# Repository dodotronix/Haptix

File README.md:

## HAPTIX

### INSTALL
* install Archlinux on SD card (https://archlinuxarm.org/platforms/armv6/raspberry-pi)
* turn on RPi
* use ssh or keyboard and display to continue in installation

* update system with
> pacman -Syu
* download 
> pacman -S python 
* download snap shot from link: https://aur.archlinux.org/packages/python-spidev/
* open terminal -> cd /path/to/file -> tar xzf file-name -> cd file-name ->
makepkg -s -> sudo pacman -U name-of-file.pkg.tar.xz
* copy test.py to raspberry
* cd /path/to/test.py
* chmod +x test.py
* ./test.py
* you select functions in script, which you want to run

### NOTES
* spidev doc (https://github.com/doceme/py-spidev)
* raspberry ssh command: ssh alarm@10.0.4.x, password: "alarm" (custom settings)
* sudo iptables -t nat -vnL
* setup.sh creates nat, starts dhcpcd, launchs ssh (parameters: on/off)

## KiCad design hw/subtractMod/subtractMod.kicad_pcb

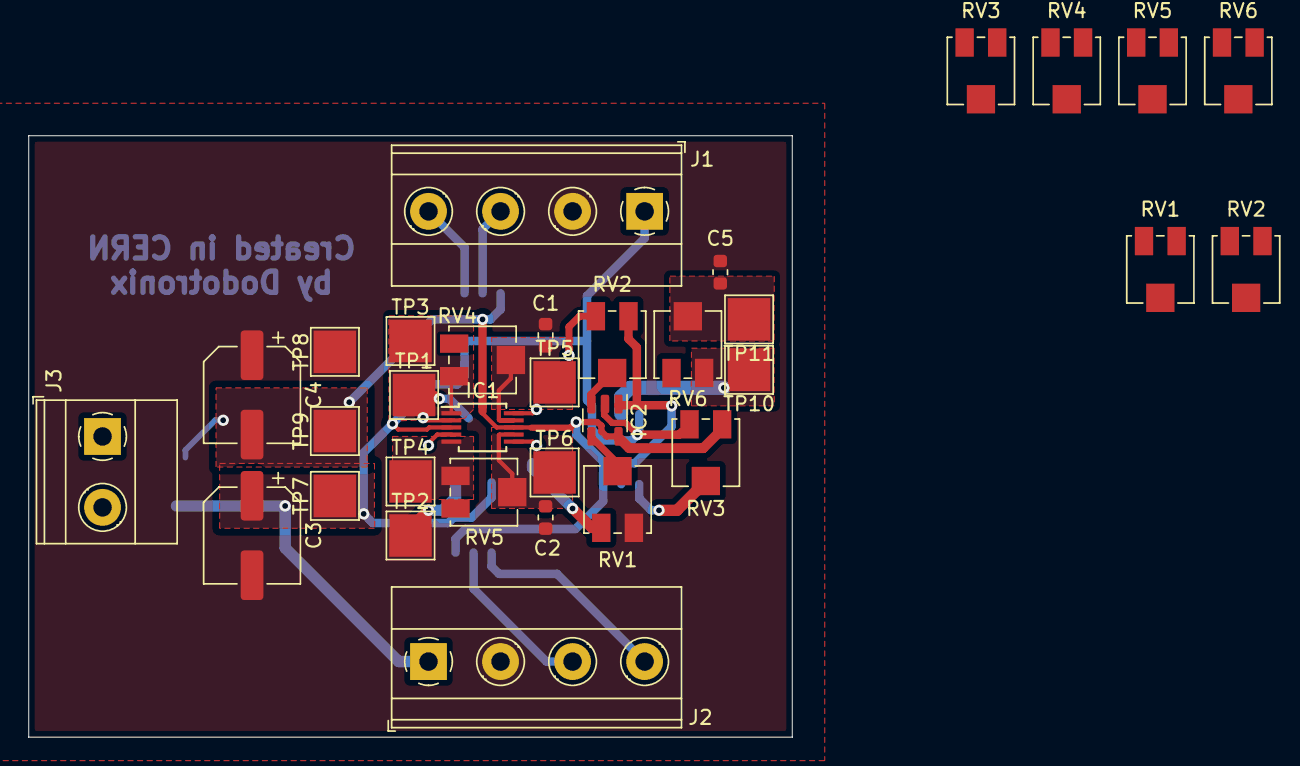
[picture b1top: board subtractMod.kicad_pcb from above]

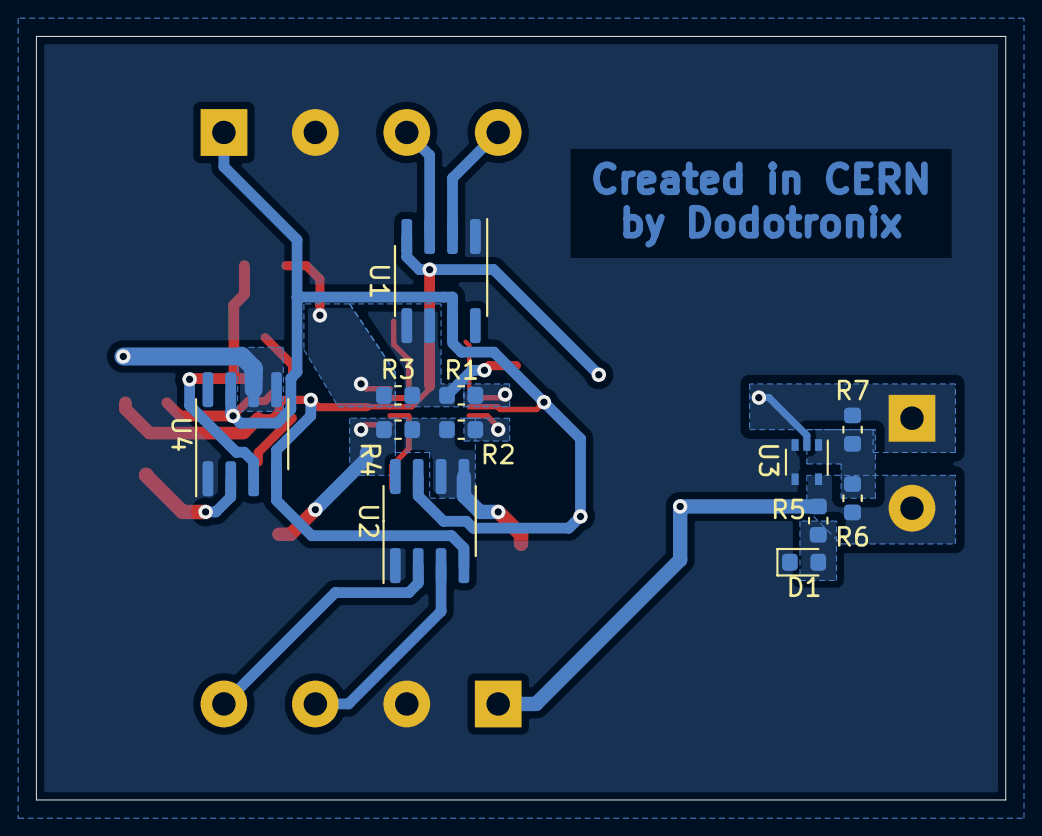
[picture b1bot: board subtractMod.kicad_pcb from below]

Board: 2 copper layers, 53.8 x 42.4 mm, 45 parts (12 on the bottom side), 25 nets.

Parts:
C1, C2, C5: C; C_0603_1608Metric
C3, C4: 47u; CP_Elec_6.3x5.9
D1: LED; LED_0603_1608Metric
IC1: AD8244; MSOP-10_3x3mm_P0.5mm
IC2: LMP2011; SOT-23-5
J1, J2: Screw_Terminal_01x04; TerminalBlock_Phoenix_MKDS-1,5-4-5.08_1x04_P5.08mm_Horizont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
J3: Screw_Terminal_01x02; TerminalBlock_Phoenix_MKDS-1,5-2_1x02_P5.00mm_Horizontal
R1, R2, R3, R4: 0R; R_0603_1608Metric
R5: R; R_0603_1608Metric
R6, R7: 10k; R_0603_1608Metric
RV1, RV2, RV3, RV4, RV5, RV6: R_POT_TRIM; Potentiometer_Bourns_3314J_Vertical
RV1#2, RV2#2, RV3#2, RV4#2, RV5#2, RV6#2: R_Potentiometer_Trim; Potentiometer_Bourns_3314J_Vertical
TP1, TP2, TP3, TP4, TP5, TP6, TP7, TP8, TP9, TP10, TP11: TestPoint; TestPoint_Pad_3.0x3.0mm
U1, U2, U4: AD8276; SOIC-8_3.9x4.9mm_P1.27mm
U3: TLV6001DCK; SOT-353_SC-70-5

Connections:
+5V: C3.1, IC1.3 (+V), IC2.5 (+V), J1.1, J2.1, J3.2, R5.1, R6.1, RV3.3, RV5#2.1, TP7.1, U1.7 (V+), U2.7 (V+), U3.5 (V+), U4.7 (V+)
-5V: C4.2, IC1.8 (-V), IC2.2 (-V), J3.1, R7.2, RV3.1, RV5#2.3, TP9.1, U1.4 (V-), U2.4 (V-), U3.2 (V-), U4.4 (V-)
/Input_channel/chan1_out: IC1.4 (OutB), R3.1, RV3#2.3
/Input_channel/chan2_out: IC1.9 (OutD), R4.1, RV4#2.1
/Input_channel/sensA_out: R1.2, R3.2, TP1.1, U1.5 (SENSE), U1.6
/Input_channel/sensB_out: R2.2, R4.2, TP2.1, U2.5 (SENSE), U2.6
GND: C1.2, C2.2, C3.2, C4.1, C5.2, D1.1 (K), J1.2, J2.2, RV1.3, RV4#2.3, TP8.1, U1.1 (REF), U2.1 (REF), U3.3 (-), U3.4, U4.1 (REF)
unnamed: C5.1, RV6.2, RV6#2.2, TP11.1
unnamed: D1.2 (A), R5.2
unnamed: IC1.1 (InA), R1.1
unnamed: IC1.2 (OutA), RV1#2.1, TP3.1
unnamed: C1.1, IC1.5 (InB), RV1#2.2, TP5.1
unnamed: IC1.6 (InC), R2.1
unnamed: IC1.7 (OutC), RV2#2.1, TP4.1
unnamed: C2.1, IC1.10 (InD), RV2#2.2, TP6.1
unnamed: IC2.3 (V+), RV3#2.2
unnamed: IC2.4 (V-), RV4#2.2
unnamed: IC2.1 (Vout), RV3#2.1, U4.3 (+)
unnamed: J1.3, U1.3 (+)
unnamed: J1.4, U1.2 (-)
unnamed: J2.3, U2.3 (+)
unnamed: J2.4, U2.2 (-)
unnamed: R6.2, R7.1, U3.1 (+)
unnamed: RV5#2.2, U4.2 (-)
unnamed: RV6#2.1, TP10.1, U4.5 (SENSE), U4.6

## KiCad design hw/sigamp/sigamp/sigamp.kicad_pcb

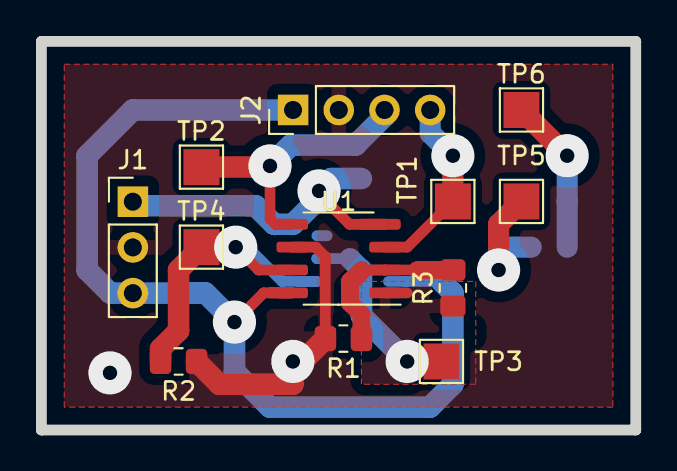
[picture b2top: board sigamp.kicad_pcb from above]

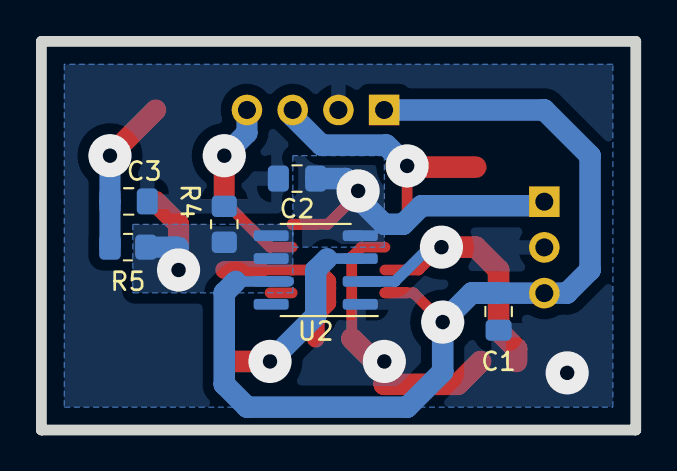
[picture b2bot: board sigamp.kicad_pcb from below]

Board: 2 copper layers, 33.0 x 21.6 mm, 18 parts (6 on the bottom side), 10 nets.

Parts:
C1, C2: 100n; C_0805_2012Metric_Pad1.18x1.45mm_HandSolder
C3: C; C_0805_2012Metric_Pad1.18x1.45mm_HandSolder
J1: Conn_01x03; PinHeader_1x03_P2.54mm_Vertical
J2: Conn_01x04; PinHeader_1x04_P2.54mm_Vertical
R1, R2, R3, R4, R5: R; R_0805_2012Metric_Pad1.20x1.40mm_HandSolder
TP1, TP2, TP3, TP4, TP5, TP6: TestPoint; TestPoint_Pad_2.0x2.0mm
U1: LM358; SO-8_3.9x4.9mm_P1.27mm
U2: AD8276; SOIC-8_3.9x4.9mm_P1.27mm

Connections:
+5V: C1.1, J1.3, J2.1, U1.8 (V+), U2.7 (V+)
-5V: C2.1, J1.1, U1.4 (V-), U2.4 (V-)
/s+: J2.4, TP1.1, U1.3 (+)
/s-: J2.3, TP2.1, U1.5 (+)
GND: C1.2, C2.2, C3.2, J1.2, J2.2, R1.2, R2.1, R4.1, U1.6 (-), U2.1 (REF)
unnamed: C3.1, R5.1, TP6.1
unnamed: R1.1, R3.2, U1.2 (-)
unnamed: R2.2, TP4.1, U1.7, U2.2 (-)
unnamed: R3.1, TP3.1, U1.1, U2.3 (+)
unnamed: R4.2, R5.2, TP5.1, U2.5 (SENSE), U2.6

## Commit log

2018-12-14 new project
2018-12-14 new readme
2018-12-18 spi test
2018-12-19 hardware photos
2018-12-24 new functions
2018-12-26 installation guide
2018-12-26 new functions in script for analysis
2018-12-26 scheme of wiring of DUT
2020-02-29 pcb for signal subtraction test
2020-02-29 new gitignore
2020-03-02 changed tracks width
2020-03-11 added component webpages and datasheets
2020-03-11 reorganizing of onboard pins
2021-06-15 signal amplifier for load cell sensor reliability test
2024-09-06 created new empty script to simulate kinematics of the grinder
2024-09-10 basic speed chart respecting the system parameters
2024-09-10 fixed wrong calculation of the decelation stage
2024-09-10 finished simulation of the speed when the movable part reaches the top
2024-09-11 model is now reacting to change of the tool height
2024-09-13 refactored kinematic_model script and renamed to demo.m
2024-09-13 adjusted plots to be easier to read
2024-09-13 added gforce
2024-09-13 added force chart which we need for further simulation
2024-09-13 added contra force signal, that is simulating the force applied to the tool from above
2024-09-14 fixed problem with cumtrapez, which did not return correct number of values
2024-09-14 removed redundant printouts
2024-09-14 messing around with possible scenarios of interference
2024-09-17 blink test python script using ft232h
2024-09-17 added i2c class to control the accelerometer
2024-09-17 added makefile to install important libraries and packages
2024-09-17 prototype of pkgbuild for bno08x library for archlinux
2024-09-17 package to build latest circuitpython bno08x library
2024-09-17 busdevice pkgbuild moved to dedicated folder
2024-09-17 created new arch package circuitpython-busdevice
2024-09-17 created new package circuitpython-typing
2024-09-18 fixed wrong name of the adafruit python package
2024-09-21 tested different speeds of i2c - chip uses stretching and lower clock speed does not work
2024-09-21 added spi, it seems to be responding, but the ft232h bridge does not support cpha=1
2024-09-21 ft232h seems to work with mpu6050 accelerometer
2024-09-21 new bno08x circuitpython library for archlinux
2024-09-21 new mpu6050 circuitpython library for archlinux
2024-09-21 new circuitpython register library for archlinux
2024-09-25 deleted redundant bno08x package
2024-09-25 fixed wrong conflits and added suffix git to each directory
2024-09-25 missing circuitpython in the package name
2024-09-28 added pyvisa to dependencies
2024-09-28 script reading waveform from my rigol oscilloscope
2024-09-30 updated kicad file version
2024-10-05 scripts for haptix tests
2024-10-05 updated schematics of subtraction module
2024-10-14 removed ft232h bridge
2024-10-14 created circuit python accelerometer and storage test
2024-10-17 added network configuration to connect rigol to my computer
2024-10-18 working measurement setup
2024-10-18 measurement in micrometers of the force sensor
2024-10-22 load cell and accelerometer tests
2024-10-25 last code.py update
2024-11-19 removed redundant measurements
2024-11-20 removed nonsens data
2024-11-20 created demo for analyzing measured data
2024-11-21 substraction demo script to test detection method
2024-11-22 unsorted force measurements moved to touch_4 folder
2024-11-22 light hand touches analysis
2024-11-24 data measured with the ltc2440 moved to the other measurements
2024-11-24 reorganized data loading
2024-11-24 created test to analyze interferences - not working, because of incorrect data collection for the first test
2024-11-30 kalman filter test from the book
2024-11-30 kalmanfilter test demo on real data
2024-12-01 added empty matrices
2024-12-05 created demo to try to guess the impulse response of the system
2024-12-05 kalman demos
2024-12-15 octave demos to play with different features
2024-12-15 testing envelop tracking
2025-01-24 schematics of the new attempts to use instrumentation amplifier and analog accelerometer
2025-02-27 updated contact array circuit
2025-02-27 deleted redundant data
2025-02-27 measured shaking signals on the table setup
2025-02-27 other attempts to clear out the vibrations
2025-03-03 rigol programming manual
2025-03-03 adjusted code to test accelerometer and load cell data processing
2025-03-03 updated version of kicad
2025-03-03 table demo data processing
2025-03-29 table setup tests
2025-03-29 lms demo
2025-04-06 data readout small qt app to test the LMS
2025-04-07 removed log messages
2025-04-08 reading test of the mcp3008 from the analog discovery 3
    There is no way to read the data with regular time stamps, so the
    bandwidth of the readout is too low for 3khz vibration signal
2025-04-09 haptix arduino uno r3 test
2025-04-10 updated - the adafruit library supports just spi freq 1MSmp, timer set to 150us (~6khz)
2025-04-11 code to visualise data read from the mcp3008 adc using arduino
2025-04-11 deleted redundant scripts
2025-04-11 added some comments and changed configs for the AD3
2025-04-11 table setup data in the lab
2025-04-11 new demo to check the matching of the two sensors signals
2025-04-11 added time axis to the demo
2025-04-11 updated kicad version
2025-04-11 added plot of old data to compare results
2025-04-16 new feature: save data
2025-04-17 loaded new data with sampled vibration process measured on the arduino setup
2025-04-17 arduino setup vibration process data
2025-04-20 created pycharm project to analyze all the properties of the measured signal
2025-05-02 created butterworth c implementation test
2025-05-02 added input delay to the butterworth filter
2025-05-02 added offset initialization
2025-05-02 added ema, ema2, var and gradient calculation
2025-05-02 created prototype of the detection chain - needs to be verified in python and changed to use fixed point math
2025-05-06 this script is testing the fixed point math to be implemented on arduino
2025-05-06 small simulation of impacts of differences in both measured signals in subtraction process
2025-05-06 dsp for detection development script
2025-05-06 testing the zero-score algorithm on the scope data
2025-05-06 highlevel dsp chain development
2025-05-06 quick visual verification of the code functionality implemented partially in arduino
2025-05-06 removed channel2 which is an overkill for simple binary detection
2025-05-06 implementation of butterworth filter with delay, offset and multiplication factor
2025-05-08 detection simplified to zero-score and simple subtraction of the load cell and accelerometer signals
2025-05-08 corrected calculation of the distance the table moves before stopping
2025-05-10 removed python simulations of impulse response
2025-05-10 created prototypes of the detector and input butterworth filter on arduino - verified in python
2025-05-10 removed redundant C tests of the butterworth IIR implementation and zero-score detector
2025-05-11 arduino core application moved to arduino folder
2025-05-11 simple butterworth filtering, scaling and subtraction of the signals
2025-05-11 generated iir constants for cutoff freq 120Hz
2025-05-11 first version of the detection procedure on arduino - not tunned yet
2025-05-11 used butter function to generate real coefficients for the iir
2025-05-11 division after avg and var update resolved through macro
2025-05-12 removed outdated dsp arduino python simulation
2025-05-12 processing chain development using fixed point and lut to calculate sqrt, includes cross-check of the fixed point math
2025-05-12 added sqrt LUT to calculate quickly the sqrt(varSum)
2025-05-12 printing the extended version of aa and bb variables to calculate varSum
2025-05-12 the translation of the variance using the LUT had to be moved behind the zero limit condition
2025-05-13 print out the sqrt_q LUT table to be able to upload it to arduino
2025-05-13 python cannot bitshift correctly negative number down to zero - it has to be done using if statement
2025-05-13 ema shifts reduced to one
2025-05-14 updated detector processing to reduce number of bitshifts - cross-checked with the python script
2025-05-14 upgraded detector fixing issues with rounding errors because of too many bitshifts
2025-05-14 added fixed point LUT sqrt generation, and fixed point aritmethic compared with floating math
2025-05-14 measured signal samples to tune the detector settings in python
2025-05-14 notes, how the contact array design works with Analog Discovery 3
2025-05-15 changed iir constant datatype to int32_t, new fmul and removed uint32_t datatypes
2025-05-15 implemented iir using for loops to be able to compare intermediate calculations
2025-05-15 first version of the small demo - the parameters need to be tuned a bit
2025-05-15 cutoff of the iir reduced to 30Hz for better accelerometer and force signal overlap
2025-05-15 updated arduino script to match the python script settings
2025-05-16 added input force sample set to be able to translate force to weight and normalized with 8bit sample width
2025-05-16 added weight calibration data set with different amplification factor
